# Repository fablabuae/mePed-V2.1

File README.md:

# mePed-V2.1

Contributed by **Hashem Al Sakkaf**  

A mePed V2.0 version with tiny modification based on the mePed V2.0 by **meped.io**  

This project was done in **Super FabLab** UAE by Hashem Al Sakkaf for Electronics Assembly challenge during Emirates Skills 2018 Competition.

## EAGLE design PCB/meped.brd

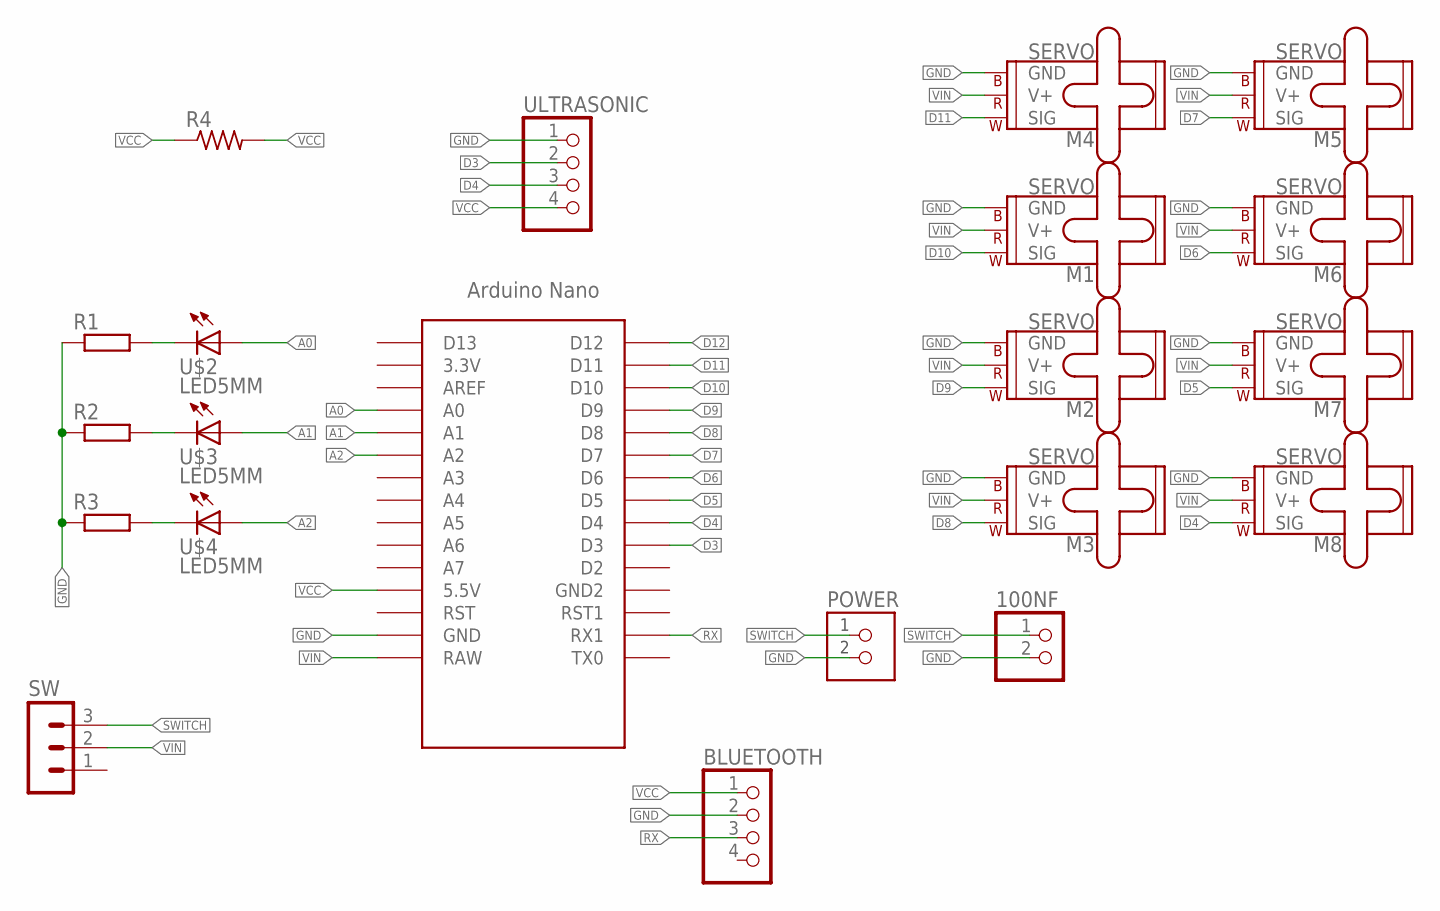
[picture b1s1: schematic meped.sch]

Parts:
100NF: PINHD-1X2; 1X02
BLUETOOTH: PINHD-1X4; 1X04
M1, M2, M3, M4, M5, M6, M7, M8: SERVO; 1X03
POWER: TERM-1X02-ADAFRUIT; 3.5MMTERM
R1, R2, R3: R-EU_0204/5; 0204/5
R4: RES-US1206FAB; R1206FAB
SW: MA03-1
U$1: NANO
U$2, U$3, U$4: LED5MM; 5MM
ULTRASONIC: PINHD-1X4; 1X04

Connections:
A0: U$1.A0, U$2.IN (A)
A1: U$1.A1, U$3.IN (A)
A2: U$1.A2, U$4.IN (A)
D3: U$1.D3, ULTRASONIC.2
D4: M8.1 (SIG), U$1.D4, ULTRASONIC.3
D5: M7.1 (SIG), U$1.D5
D6: M6.1 (SIG), U$1.D6
D7: M5.1 (SIG), U$1.D7
D8: M3.1 (SIG), U$1.D8
D9: M2.1 (SIG), U$1.D9
D10: M1.1 (SIG), U$1.D10
D11: M4.1 (SIG), U$1.D11
D12: U$1.D12
GND: 100NF.2, BLUETOOTH.2, M1.3 (GND), M2.3 (GND), M3.3 (GND), M4.3 (GND), M5.3 (GND), M6.3 (GND), M7.3 (GND), M8.3 (GND), POWER.2, R1.1, R2.1, R3.1, U$1.GND, ULTRASONIC.1
unnamed: R1.2, U$2.OUT (C)
unnamed: R2.2, U$3.OUT (C)
unnamed: R3.2, U$4.OUT (C)
RX: BLUETOOTH.3, U$1.RX1
SWITCH: 100NF.1, POWER.1, SW.3
VCC: BLUETOOTH.1, R4.1, R4.2, U$1.5V (5.5V), ULTRASONIC.4
VIN: M1.2 (V+), M2.2 (V+), M3.2 (V+), M4.2 (V+), M5.2 (V+), M6.2 (V+), M7.2 (V+), M8.2 (V+), SW.2, U$1.RAW

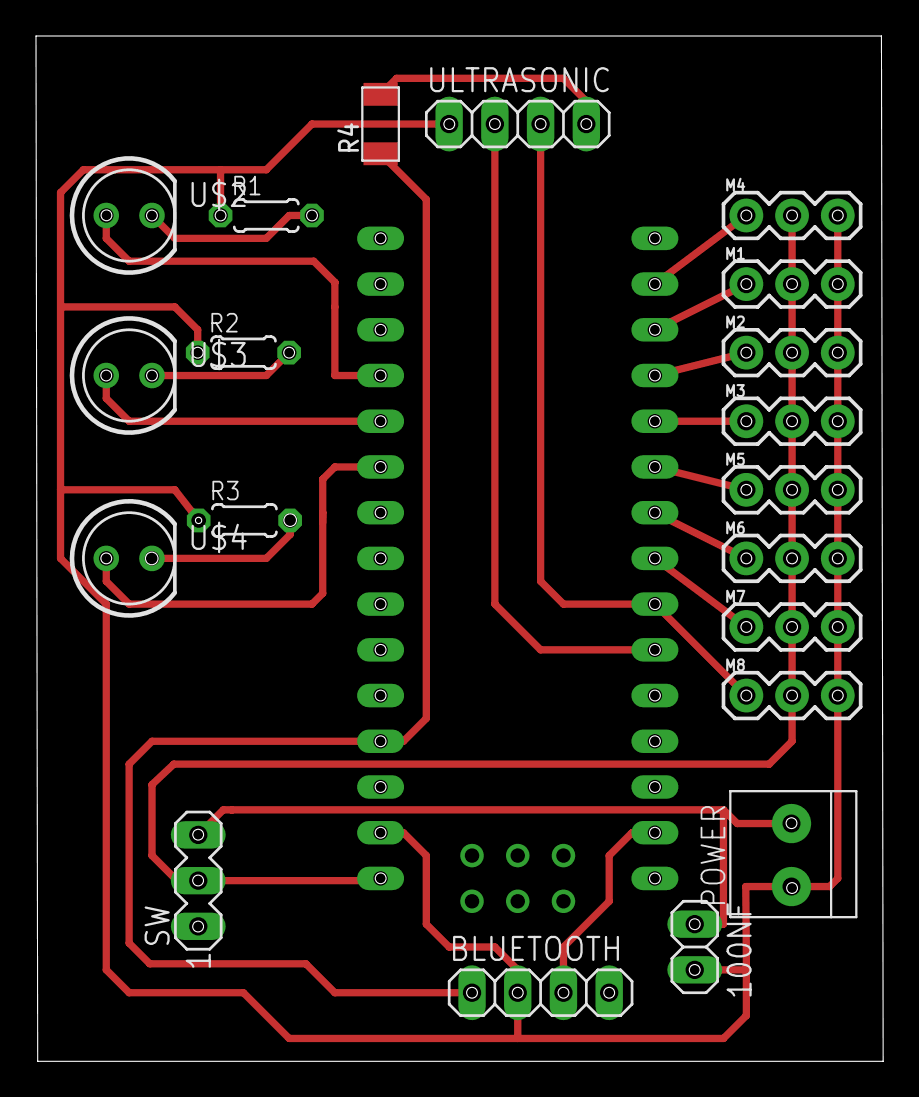
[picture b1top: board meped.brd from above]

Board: 2 copper layers, 47.1 x 57.0 mm, 21 parts (0 on the bottom side), 20 nets.

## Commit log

2018-05-03 added the initial files
2018-05-03 added the assembly isntructions
2018-05-03 edited the read me file

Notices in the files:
parts and their libraries:
SparkFun-Electromechanical: Licensing: Creative Commons ShareAlike 4.0 International - https://creativecommons.org/licenses/by-sa/4.0
